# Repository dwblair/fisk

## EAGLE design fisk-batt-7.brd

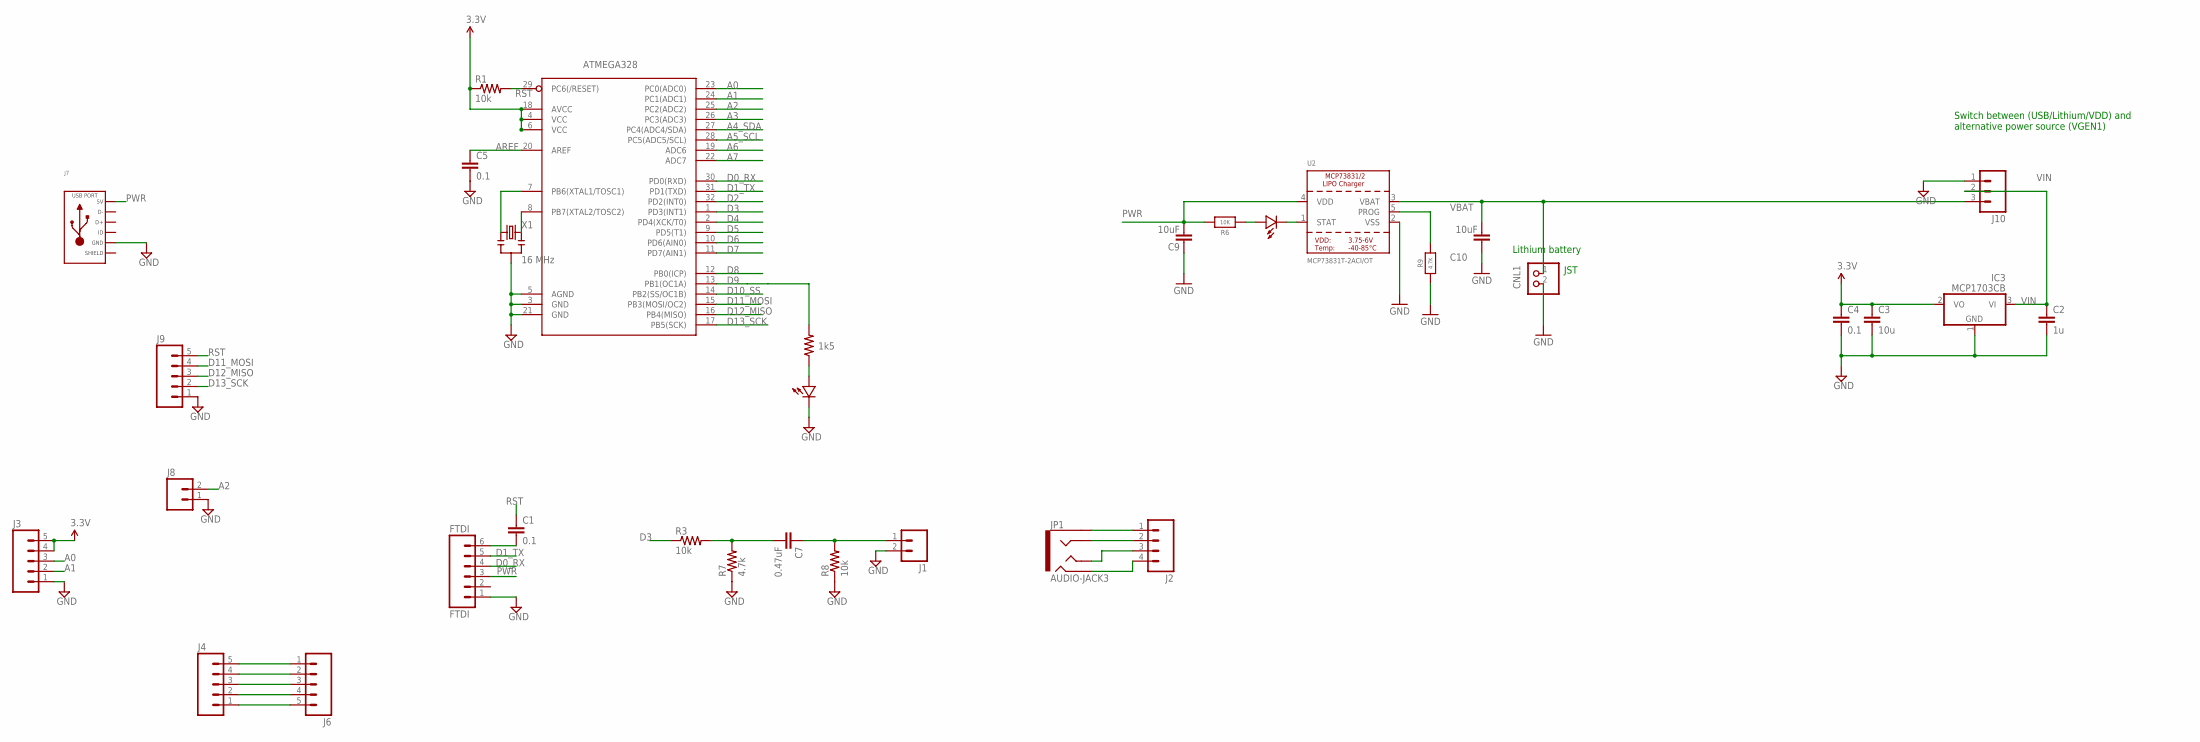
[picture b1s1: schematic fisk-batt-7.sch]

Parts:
ATMEGA328: ATMega-328; TQFP32-08
C1, C4, C5: 0.1; 0603-CAP
C2: 1u; 0603-CAP
C3: 10u; 0805-CAP
C7: 0.47uF; 0603-CAP
C9, C10: 10uF; 0603-CAP
CNL1: JST_2PIN-SMT-RA; JST-PH-2-SMT-RA
D2: LED0603; 0603-LED
FTDI: FTDI; 1X06
IC3: MCP1703CB; SOT23
J1, J8: M02PTH; 1X02
J2: M04PTH; 1X04
J3, J4, J9: M05PTH; 1X05
J6: M05SCREW; SCREWTERMINAL-3.5MM-5
J7: USB_MICRO_RIGHT; MICROUSB-RIGHT
J10: M03PTH; 1X03
JP1: AUDIO-JACK3; AUDIO-JACK-TRRS-SMD
R1, R3, R8: 10k; 0603-RES
R2: 1k5; 0603-RES
R6: 10K; 0603-NO
R7: 4.7k; 0603-RES
R9: 4.7K; 0603-NO
U2: MCP73831T-2ACI/OT; SOT23-5
U$2: LED0603; 0603-LED
X1: 16 MHz; RESONATOR-SMD

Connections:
A0: ATMEGA328.23 (PC0(ADC0)), J3.3
A1: ATMEGA328.24 (PC1(ADC1)), J3.2
A2: ATMEGA328.25 (PC2(ADC2)), J8.2
A3: ATMEGA328.26 (PC3(ADC3))
A4_SDA: ATMEGA328.27 (PC4(ADC4/SDA))
A5_SCL: ATMEGA328.28 (PC5(ADC5/SCL))
A6: ATMEGA328.19 (ADC6)
A7: ATMEGA328.22 (ADC7)
AREF: ATMEGA328.20 (AREF), C5.1
D0_RX: ATMEGA328.30 (PD0(RXD)), FTDI.4
D1_TX: ATMEGA328.31 (PD1(TXD)), FTDI.5
D2: ATMEGA328.32 (PD2(INT0))
D3: ATMEGA328.1 (PD3(INT1)), R3.1
D4: ATMEGA328.2 (PD4(XCK/T0))
D5: ATMEGA328.9 (PD5(T1))
D6: ATMEGA328.10 (PD6(AIN0))
D7: ATMEGA328.11 (PD7(AIN1))
D8: ATMEGA328.12 (PB0(ICP))
D9: ATMEGA328.13 (PB1(OC1A)), R2.2
D10_SS: ATMEGA328.14 (PB2(SS/OC1B))
D11_MOSI: ATMEGA328.15 (PB3(MOSI/OC2)), J9.4
D12_MISO: ATMEGA328.16 (PB4(MISO)), J9.3
D13_SCK: ATMEGA328.17 (PB5(SCK)), J9.2
GND: ATMEGA328.3 (GND), ATMEGA328.5 (AGND), ATMEGA328.21 (GND), C2.2, C3.2, C4.2, C5.2, C9.2, C10.2, CNL1.2 (1), FTDI.1, IC3.1 (GND), J1.2, J3.1, J7.5 (GND), J8.1, J9.1, J10.1, R7.1, R8.1, R9.1, U2.2 (VSS), U$2.MINUS, X1.2; also elsewhere on the board
unnamed: ATMEGA328.7 (PB6(XTAL1/TOSC1)), X1.1
unnamed 25: R2.1, U$2.PLUS; also elsewhere on the board
unnamed: C7.2, R3.2, R7.2
unnamed: C7.1, J1.1, R8.2
unnamed: J2.1, JP1.EARTH
unnamed: J2.2, JP1.RING1
unnamed: J2.3, JP1.TIP
unnamed: J2.4, JP1.RING2
unnamed: J4.5, J6.1
unnamed: J4.4, J6.2
unnamed: J4.3, J6.3
unnamed: J4.2, J6.4
unnamed: J4.1, J6.5
unnamed: R9.2, U2.5 (PROG)
unnamed: D2.MINUS, U2.1 (STAT)
unnamed: D2.PLUS, R6.1
unnamed: C1.2, FTDI.6
unnamed: ATMEGA328.8 (PB7(XTAL2/TOSC2)), X1.3
PWR: C9.1, FTDI.3, J7.1 (5V), R6.2, U2.4 (VDD)
RST: ATMEGA328.29 (PC6(/RESET)), C1.1, J9.5, R1.2
SLD: J7.S1 (SLD), J7.S2 (SLD), J7.S3 (SLD), J7.S4 (SLD), J7.S5 (SLD), J7.S6 (SLD), J7.S7 (SLD), J7.S8 (SLD)
VBAT: C10.1, CNL1.1 (2), J10.3, U2.3 (VBAT)
VCC: ATMEGA328.4 (VCC), ATMEGA328.6 (VCC), ATMEGA328.18 (AVCC), C3.1, C4.1, IC3.2 (VO), J3.4, J3.5, R1.1
VIN: C2.1, IC3.3 (VI), J10.2

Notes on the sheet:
Lithium battery
JST
Switch between (USB/Lithium/VDD) and alternative power source (VGEN1)

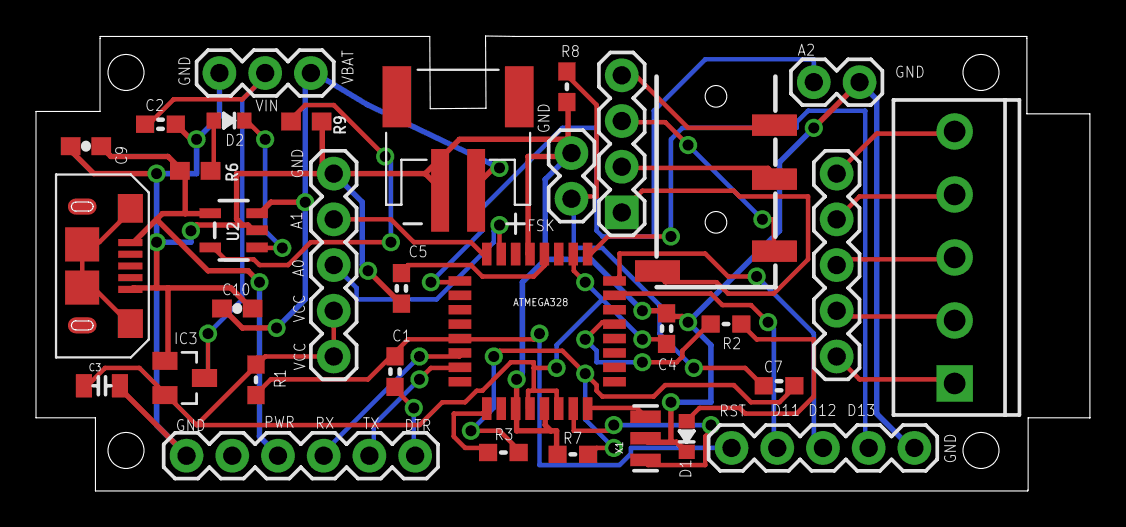
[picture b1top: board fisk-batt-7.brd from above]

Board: 2 copper layers, 58.5 x 25.3 mm, 33 parts (0 on the bottom side), 36 nets.

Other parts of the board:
D1: LED0603; 0603-LED

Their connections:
GND: D1.MINUS; also elsewhere on the board
unnamed 25: D1.PLUS; also elsewhere on the board

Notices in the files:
parts and their libraries:
SparkFun-Connectors: Licensing: CC v3.0 Share-Alike You are welcome to use this library for commercial purposes.
microbuilder: This work is placed in the public domain, and may be freely used for commercial and non-commercial work with the following conditions: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
